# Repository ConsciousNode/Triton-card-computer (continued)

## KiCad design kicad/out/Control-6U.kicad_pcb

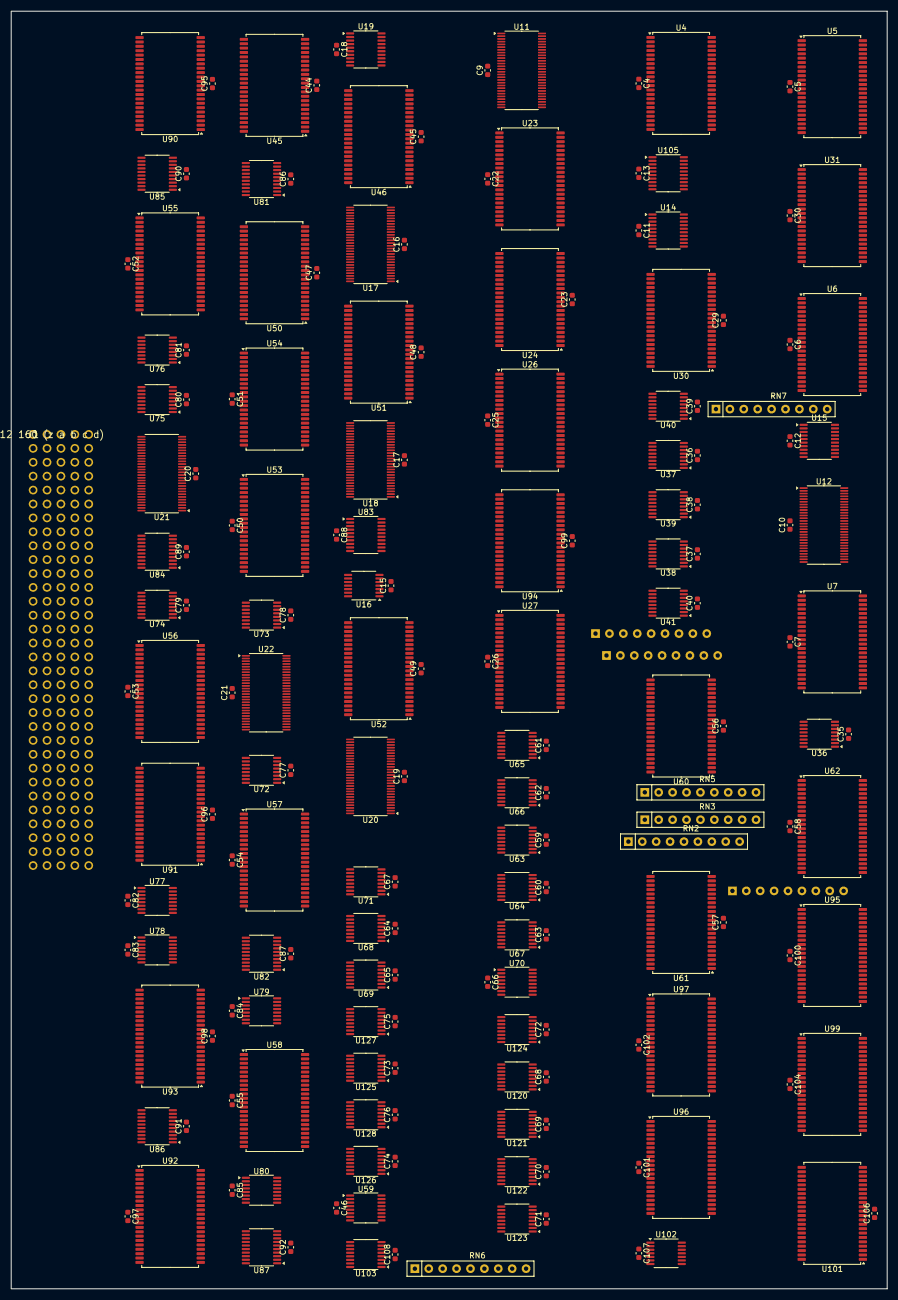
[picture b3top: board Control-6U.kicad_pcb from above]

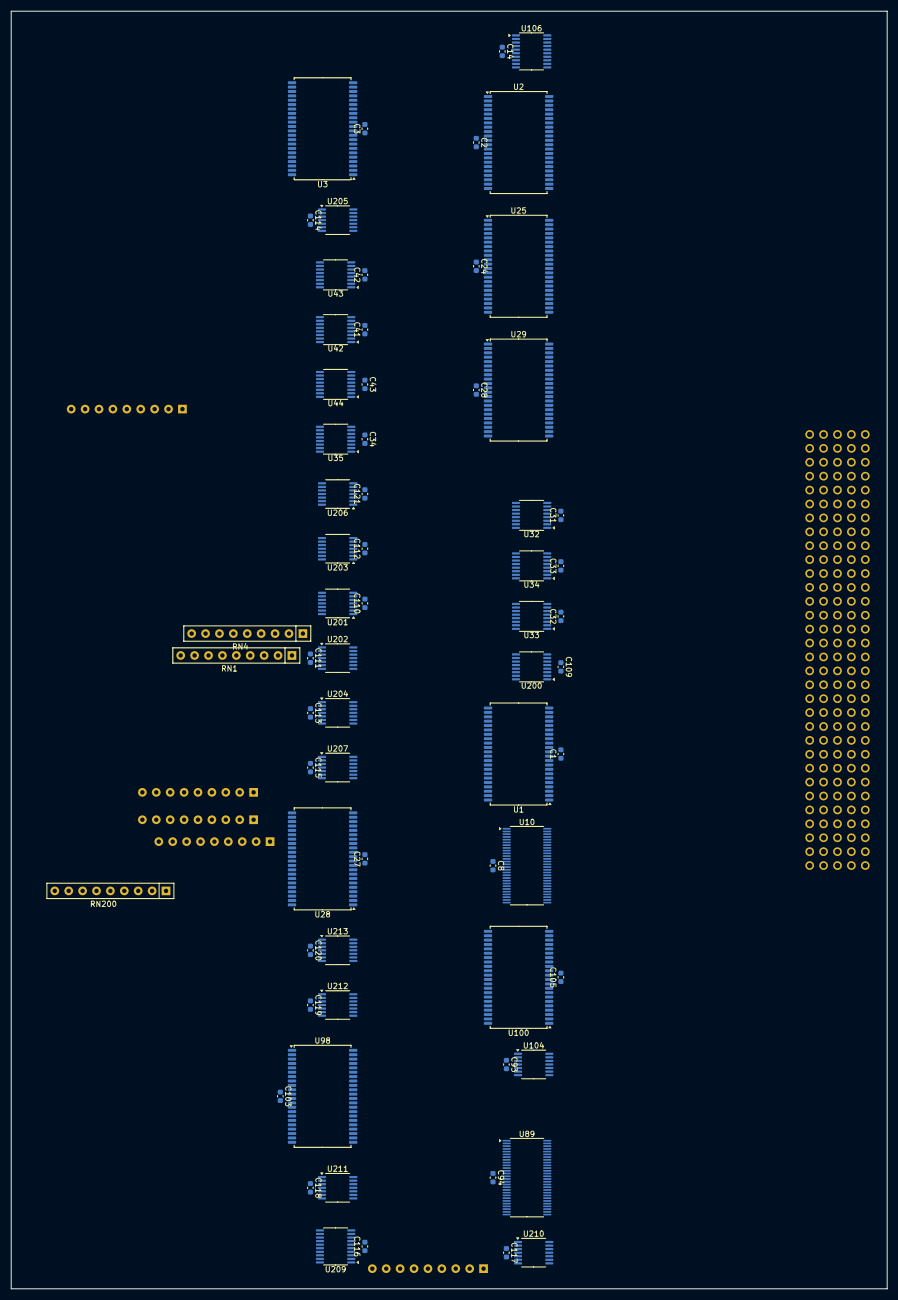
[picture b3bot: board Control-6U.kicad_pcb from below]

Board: 4 copper layers, 160.0 x 233.3 mm, 251 parts (67 on the bottom side), 680 nets, no tracks yet.

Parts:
C1, C2, C3, C4, C5, C6, C7, C8, C9, C10, C11, C12, C13, C14, C15, C16, C17, C18, C19, C20, C21, C22, C23, C24, C25, C26, C27, C28, C29, C30, C31, C32, C33, C34, C35, C36, C37, C38, C39, C40, C41, C42, C43, C44, C45, C46, C47, C48, C49, C50, C51, C52, C53, C54, C55, C56, C57, C58, C59, C60, C61, C62, C63, C64, C65, C66, C67, C68, C69, C70, C71, C72, C73, C74, C75, C76, C77, C78, C79, C80, C81, C82, C83, C84, C85, C86, C87, C88, C89, C90, C91, C92, C93, C94, C95, C96, C97, C98, C99, C100, C101, C102, C103, C104, C105, C106, C107, C108, C109, C110, C111, C112, C113, C114, C115, C116, C117, C118, C119, C120, C121: 100n; C_0603_1608Metric
J1: DIN41612 160 (z a b c d)
RN1, RN2, RN3, RN4, RN5, RN6, RN7: RPACK8; R_Array_SIP9
RN200: RPACK8G; R_Array_SIP9
U1, U2, U3, U4, U5, U6, U7, U23, U24, U25, U26, U27, U28, U29, U30, U31, U45, U46, U50, U51, U52, U53, U54, U55, U56, U57, U58, U60, U61, U62, U90, U91, U92, U93, U94, U95, U96, U97, U98, U99, U100, U101: IS61WV5128; TSOP-II-44_10.16x18.41mm_P0.8mm
U10, U11, U12, U17, U18, U20, U21, U22, U89: ALVCH16823; TSSOP-56_6.1x14mm_P0.5mm
U14, U15, U19, U209: LVC574; TSSOP-20_4.4x6.5mm_P0.65mm
U16, U203, U212: LVC32; TSSOP-14_4.4x5mm_P0.65mm
U32, U33, U34, U35, U36, U37, U38, U39, U40, U41, U42, U43, U44, U63, U64, U65, U66, U67, U68, U69, U70, U71, U120, U121, U122, U123, U124, U125, U126, U127, U128: LVC153; TSSOP-16_4.4x5mm_P0.65mm
U59, U72, U73, U74, U75, U76, U77, U78, U79, U80, U103: LVC157; TSSOP-16_4.4x5mm_P0.65mm
U81, U82, U83, U84, U85, U86, U87: LVC245; TSSOP-20_4.4x6.5mm_P0.65mm
U102, U202, U207, U211: LVC08; TSSOP-14_4.4x5mm_P0.65mm
U104, U201, U210: LVC04; TSSOP-14_4.4x5mm_P0.65mm
U105, U106: LVC244; TSSOP-20_4.4x6.5mm_P0.65mm
U200: LVC161; TSSOP-16_4.4x5mm_P0.65mm
U204, U205, U206, U213: LVC74; TSSOP-14_4.4x5mm_P0.65mm

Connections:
+3V3: C1.1, C2.1, C3.1, C4.1, C5.1, C6.1, C7.1, C8.1, C9.1, C10.1, C11.1, C12.1, C13.1, C14.1, C15.1, C16.1, C17.1, C18.1, C19.1, C20.1, C21.1, C22.1, C23.1, C24.1, C25.1, C26.1, C27.1, C28.1, C29.1, C30.1, C31.1, C32.1, C33.1, C34.1, C35.1, C36.1, C37.1, C38.1, C39.1, C40.1, C41.1, C42.1, C43.1, C44.1, C45.1, C46.1, C47.1, C48.1, C49.1, C50.1, C51.1, C52.1, C53.1, C54.1, C55.1, C56.1, C57.1, C58.1, C59.1, C60.1, C61.1, C62.1, C63.1, C64.1, C65.1, C66.1, C67.1, C68.1, C69.1, C70.1, C71.1, C72.1, C73.1, C74.1, C75.1, C76.1, C77.1, C78.1, C79.1, C80.1, C81.1, C82.1, C83.1, C84.1, C85.1, C86.1, C87.1, C88.1, C89.1, C90.1, C91.1, C92.1, C93.1, C94.1, C95.1, C96.1, C97.1, C98.1, C99.1, C100.1, C101.1, C102.1, C103.1, C104.1, C105.1, C106.1, C107.1, C108.1, C109.1, C110.1, C111.1, C112.1, C113.1, C114.1, C115.1, C116.1, C117.1, C118.1, C119.1, C120.1, C121.1, J1.z2, J1.z4, J1.z6, J1.z10, J1.z12, J1.z14, J1.z18, J1.z20, J1.z22, J1.z26, J1.z28, J1.z30, RN1.1, RN2.1, RN3.1, RN4.1, RN5.1, RN6.1, RN7.1, U1.11, U1.15, U1.33, U2.11, U2.15, U2.33, U3.11, U3.15, U3.33, U4.11, U4.15, U4.33, U5.11, U5.15, U5.33, U6.11, U6.15, U6.33, U7.11, U7.15, U7.33, U10.1, U10.7, U10.22, U10.28, U10.35, U10.50, U11.1, U11.7, U11.22, U11.28, U11.35, U11.50, U12.1, U12.7, U12.22, U12.28, U12.35, U12.50, U14.20, U15.20, U16.14, U17.1, U17.7, U17.22, U17.28, U17.35, U17.50, U18.1, U18.7, U18.22, U18.28, U18.35, U18.50, U19.20, U20.1, U20.7, U20.22, U20.28, U20.35, U20.50, U21.1, U21.7, U21.22, U21.28, U21.35, U21.50, U22.1, U22.7, U22.22, U22.28, U22.35, U22.50, U23.11, U23.15, U23.33, U24.11, U24.15, U24.33, U25.11, U25.15, U25.33, U26.11, U26.15, U26.33, U27.11, U27.15, U27.33, U28.11, U28.15, U28.33, U29.11, U29.15, U29.33, U30.11, U30.15, U30.33, U31.11, U31.15, U31.33, U32.3, U32.4, U32.11, U32.12, U32.13, U32.16, U33.3, U33.5, U33.11, U33.16, U34.3, U34.4, U34.11, U34.12, U34.16, U35.11, U35.12, U35.16, U36.4, U36.5, U36.13, U36.16, U37.16, U38.16, U39.16, U40.16, U41.16, U42.16, U43.16, U44.15, U44.16, U45.11, U45.15, U45.33, U46.11, U46.15, U46.33, U50.11, U50.15, U50.33, U51.11, U51.15, U51.33, U52.11, U52.15, U52.33, U53.11, U53.15, U53.33, U54.11, U54.15, U54.33, U55.11, U55.15, U55.33, U56.11, U56.15, U56.33, U57.11, U57.15, U57.33, U58.11, U58.15, U58.33, U59.2, U59.16, U60.11, U60.15, U60.33, U61.11, U61.15, U61.33, U62.11, U62.15, U62.33, U63.16, U64.16, U65.16, U66.16, U67.16, U68.16, U69.16, U70.16, U71.16, U72.16, U73.16, U74.16, U75.16, U76.16, U77.16, U78.16, U79.16, U80.16, U81.1, U81.20, U82.1, U82.20, U83.1, U83.20, U84.1, U84.20, U85.1, U85.20, U86.1, U86.20, U87.1, U87.20, U89.7, U89.22, U89.35, U89.50, U90.11, U90.15, U90.33, U91.11, U91.15, U91.33, U92.11, U92.15, U92.33, U93.11, U93.15, U93.33, U94.11, U94.15, U94.33, U95.11, U95.15, U95.33, U96.11, U96.15, U96.33, U97.11, U97.15, U97.33, U98.11, U98.15, U98.33, U99.11, U99.15, U99.33, U100.11, U100.15, U100.33, U101.11, U101.15, U101.33, U102.14, U103.16, U104.14, U105.20, U106.20, U120.16, U121.16, U122.16, U123.16, U124.16, U125.16, U126.16, U127.16, U128.16, U200.1, U200.7, U200.10, U200.16, U201.14, U202.14, U203.14, U204.1, U204.4, U204.10, U204.13, U204.14, U205.1, U205.13, U205.14, U206.1, U206.4, U206.10, U206.14, U207.14, U209.20, U210.14, U211.14, U212.14, U213.4, U213.10, U213.13, U213.14
+5V: J1.z8, J1.z16, J1.z24, J1.z32
/CBUSOE_F: U81.19, U82.19, U83.19, U84.19, U85.19, U86.19, U87.19, U103.4
/CEDGE: J1.c13, U200.9, U204.6
/HALTQ: U206.8, U207.5
/IR0LD: U16.3, U17.30, U17.55
/IR1LD: U16.6, U18.30, U18.55
/RESETC: U201.12, U206.13, U213.1
/RESET_C: U89.1, U89.28, U104.10
/RSTREQ: U201.8, U205.4, U205.10
/SCLK: U201.6, U204.11
/SPENT: U210.6, U211.13
/STEP2: U210.2, U211.2
/WSTB: J1.d1, U206.6
ABORT: J1.c15, U16.2, U16.5, U29.7, U46.30, U50.40, U51.40, U52.40, U53.40, U54.40, U55.40, U56.40, U57.40, U58.40, U95.17, U96.7, U97.7, U98.27
ALIAS: U23.32, U28.38
ALLOW: U207.13, U212.11
ALLOW0: U212.6, U212.12
BADADDR: J1.d2, U28.30
BTOPNZ: J1.c31, U28.19
CA0+: U63.7, U120.6
CA0-: U63.9, U120.10
CA1+: U64.7, U121.6
CA1-: U64.9, U121.10
CA2+: U65.7, U122.6
CA2-: U65.9, U122.10
CA3+: U66.7, U123.6
CA3-: U66.9, U123.10
CA4+: U67.7, U124.6
CA4-: U67.9, U124.10
CA5+: U68.7, U125.6
CA5-: U68.9, U125.10
CA6+: U69.7, U126.6
CA6-: U69.9, U126.10
CA7+: U70.7, U127.6
CA7-: U70.9, U127.10
CA8+: U71.7, U128.6
CA8-: U71.9, U128.10
CB0+: U81.2, U120.7
CB0-: U81.3, U120.9
CB1+: U81.4, U121.7
CB1-: U81.5, U121.9
CB2+: U81.6, U122.7
CB2-: U81.7, U122.9
CB3+: U81.8, U123.7
CB3-: U81.9, U123.9
CB4+: U82.2, U124.7
CB4-: U82.3, U124.9
CB5+: U82.4, U125.7
CB5-: U82.5, U125.9
CB6+: U82.6, U126.7
CB6-: U82.7, U126.9
CB7+: U82.8, U127.7
CB7-: U82.9, U127.9
CB8+: U83.2, U128.7
CB8-: U83.3, U128.9
CB9+: U72.4, U83.4
CB9-: U72.7, U83.5
CB10+: U72.9, U83.6
CB10-: U72.12, U83.7
CB11+: U73.4, U83.8
CB11-: U73.7, U83.9
CB12+: U73.9, U84.2
CB12-: U73.12, U84.3
CB13+: U74.4, U84.4
CB13-: U74.7, U84.5
CB14+: U74.9, U84.6
CB14-: U74.12, U84.7
CB15+: U75.4, U84.8
CB15-: U75.7, U84.9
CB16+: U75.9, U85.2
CB16-: U75.12, U85.3
CB17+: U76.4, U85.4
CB17-: U76.7, U85.5
CB18+: U76.9, U85.6
CB18-: U76.12, U85.7
CB19+: U77.4, U85.8
CB19-: U77.7, U85.9
CB20+: U77.9, U86.2
CB20-: U77.12, U86.3
CB21+: U78.4, U86.4
CB21-: U78.7, U86.5
CB22+: U78.9, U86.6
CB22-: U78.12, U86.7
CB23+: U79.4, U86.8
CB23-: U79.7, U86.9
CB24+: U79.9, U87.2
CB24-: U79.12, U87.3
CB25+: U80.4, U87.4
CB25-: U80.7, U87.5
CB26+: U80.9, U87.6
CB26-: U80.12, U87.7
CEDGE: U204.5, U207.4
CEDGE_NEXT: U202.6, U204.2
CEN: U202.10, U204.9, U211.9
CEN_D: U204.12, U207.8
CEN_D0: U207.6, U207.9
CLK: J1.c10, U10.29, U10.56, U11.29, U11.56, U12.29, U12.56, U14.11, U15.11, U17.29, U17.56, U18.29, U18.56, U19.11, U20.29, U20.56, U21.29, U21.56, U22.29, U22.56, U89.29, U89.56, U202.8, U205.3, U205.11, U206.11
COND: U28.9, U29.6
CSD0: U1.9, U10.54
CSD1: U1.10, U10.52
CSD2: U1.13, U10.51
CSD3: U1.14, U10.49
CSD4: U1.31, U10.48
CSD5: U1.32, U10.47
CSD6: U1.35, U10.45
CSD7: U1.36, U10.44
CSD8: U2.9, U10.43
CSD9: U2.10, U10.42
CSD10: U2.13, U10.41
CSD11: U2.14, U10.40
CSD12: U2.31, U10.38
CSD13: U2.32, U10.37
CSD14: U2.35, U10.36
CSD15: U2.36, U10.34
CSD16: U3.9, U10.33
CSD17: U3.10, U10.31
CSD18: U3.13, U11.54
CSD19: U3.14, U11.52
CSD20: U3.31, U11.51
CSD21: U3.32, U11.49
CSD22: U3.35, U11.48
CSD23: U3.36, U11.47
CSD24: U4.9, U11.45
CSD25: U4.10, U11.44
CSD26: U4.13, U11.43
CSD27: U4.14, U11.42
CSD28: U4.31, U11.41
CSD29: U4.32, U11.40
CSD30: U4.35, U11.38
CSD31: U4.36, U11.37
CSD32: U5.9, U11.36
CSD33: U5.10, U11.34
CSD34: U5.13, U11.33
CSD35: U5.14, U11.31
CSD36: U5.31, U12.54
CSD37: U5.32, U12.52
CSD38: U5.35, U12.51
CSD39: U5.36, U12.49
CSD40: U6.9, U12.48
CSD41: U6.10, U12.47
CSD42: U6.13, U12.45
CSD43: U6.14, U12.44
CSD44: U6.31, U12.43
CSD45: U6.32, U12.42
CSD46: U6.35, U12.41
CSD47: U6.36, U12.40
CSD48: U7.9, U12.38
CSD49: U7.10, U12.37
CSD50: U7.13, U12.36
CSD51: U7.14, U12.34
CSD52: U7.31, U12.33
CW_/ATF: RN7.6, U12.24, U211.5
CW_/CBUSOE: RN6.4, U12.12, U103.2
CW_/IR0CE: RN5.2, U11.21, U16.1
CW_/IR1CE: RN5.3, U11.23, U16.4
CW_/UPEN: RN6.5, U12.13, U72.15, U73.15, U74.15, U75.15, U76.15, U77.15, U78.15, U79.15, U80.15
CW_ACK: RN7.3, U12.20, U98.26
CW_BS0: RN6.2, U12.9, U63.14, U64.14, U65.14, U66.14, U67.14, U68.14, U69.14, U70.14, U71.14
CW_BS1: RN6.3, U12.10, U63.2, U64.2, U65.2, U66.2, U67.2, U68.2, U69.2, U70.2, U71.2
CW_BT0: RN7.4, U12.21, U120.14, U121.14, U122.14, U123.14, U124.14, U125.14, U126.14, U127.14, U128.14
CW_BT1: RN7.5, U12.23, U120.2, U121.2, U122.2, U123.2, U124.2, U125.2, U126.2, U127.2, U128.2
CW_C0: RN2.3, U10.15, U37.5, U60.3, U61.3, U62.3
CW_C1: RN2.4, U10.16, U37.11, U60.4, U61.4, U62.4
CW_C2: RN2.5, U10.17, U38.5, U60.5, U61.5, U62.5
CW_C3: RN2.6, U10.19, U38.11, U60.6, U61.6, U62.6
CW_C4: RN2.7, U10.20, U39.5, U60.7, U61.7, U62.7
CW_C5: RN2.8, U10.21, U39.11, U60.16, U61.16, U62.16
CW_C6: RN2.9, U10.23, U40.5, U60.17, U61.17, U62.17
CW_C7: RN3.2, U10.24, U40.11, U60.18, U61.18, U62.18
CW_C8: RN3.3, U10.26, U41.5, U60.19, U61.19, U62.19
CW_C9: RN3.4, U11.3, U41.11, U60.20, U61.20, U62.20
CW_C10: RN3.5, U11.5, U60.26, U61.26, U62.26
CW_C11: RN3.6, U11.6, U60.27, U61.27, U62.27
CW_C12: RN3.7, U11.8, U60.28, U61.28, U62.28
CW_C13: RN3.8, U11.9, U60.29, U61.29, U62.29
CW_CD0: RN1.7, U10.10, U28.3
CW_CD1: RN1.8, U10.12, U28.4
CW_CD2: RN1.9, U10.13, U28.5
CW_CD3: RN2.2, U10.14, U28.6
CW_CFETCH: RN1.5, U10.8, U29.18
CW_FS0: RN4.3, U11.13, U42.6
CW_FS1: RN4.4, U11.14, U42.10
CW_FS2: RN4.5, U11.15, U43.6
CW_FS3: RN4.6, U11.16, U43.10
CW_FS4: RN4.7, U11.17, U44.6
CW_PCC+: RN5.6, U12.3, U50.28
CW_PCC-: RN5.7, U12.5, U50.29
CW_PCOP0: RN5.4, U11.24, U50.30, U51.30, U52.30, U53.30, U54.30, U55.30, U56.30, U57.30, U58.30
CW_PCOP1: RN5.5, U11.26, U50.38, U51.38, U52.38, U53.38, U54.38, U55.38, U56.38, U57.38, U58.38
CW_PSW0: RN6.9, U12.17, U95.7
CW_PSW1: RN7.2, U12.19, U95.16
CW_RET: RN1.6, U10.9, U29.17
CW_RFBUS: RN6.8, U12.16, U102.2
CW_RSK0: RN4.8, U11.19, U23.3
CW_RSK1: RN4.9, U11.20, U23.4
CW_SLS0: RN3.9, U11.10, U42.14, U43.14, U44.14
CW_SLS1: RN4.2, U11.12, U42.2, U43.2, U44.2
CW_SPR: RN6.7, U12.15, U94.41
CW_SPRWR: RN6.6, U12.14, U95.3, U96.3, U97.3
CW_SQ0: RN1.2, U10.3, U29.3
CW_SQ1: RN1.3, U10.5, U29.4
CW_SQ2: RN1.4, U10.6, U29.5
CW_UOP0: RN5.8, U12.6, U46.17
CW_UOP1: RN5.9, U12.8, U46.18
D0+: J1.a1, U17.54, U18.54, U45.3, U50.17, U81.18, U90.3
D0-: J1.a2, U17.52, U18.52, U45.4, U50.18, U81.17, U90.4
D1+: J1.a3, U17.51, U18.51, U45.5, U50.19, U81.16, U90.5
D1-: J1.a4, U17.49, U18.49, U45.6, U50.20, U81.15, U90.6
D2+: J1.a5, U17.48, U18.48, U45.7, U50.26, U81.14, U90.7
D2-: J1.a6, U17.47, U18.47, U45.16, U50.27, U81.13, U90.16
D3+: J1.a7, U17.45, U18.45, U45.17, U51.17, U81.12, U90.17, U95.19
D3-: J1.a9, U17.44, U18.44, U45.18, U51.18, U81.11, U90.18, U95.20
D4+: J1.a10, U17.43, U18.43, U51.19, U82.18, U90.19, U95.26
D4-: J1.a11, U17.42, U18.42, U51.20, U82.17, U90.20, U95.27
D5+: J1.a12, U17.41, U18.41, U51.26, U82.16, U90.26
D5-: J1.a13, U17.40, U18.40, U51.27, U82.15, U90.27
D6+: J1.a14, U17.38, U18.38, U52.17, U82.14, U90.28
D6-: J1.a15, U17.37, U18.37, U52.18, U82.13, U90.29
D7+: J1.a17, U17.36, U18.36, U52.19, U82.12, U90.30
D7-: J1.a18, U17.34, U18.34, U52.20, U82.11, U90.38
D8+: J1.a19, U17.33, U18.33, U52.26, U83.18, U90.39
D8-: J1.a20, U17.31, U18.31, U52.27, U83.17, U90.40
D9+: J1.a21, U53.17, U83.16, U91.3
D9-: J1.a22, U53.18, U83.15, U91.4
D10+: J1.a23, U53.19, U83.14, U91.5
D10-: J1.a25, U53.20, U83.13, U91.6
D11+: J1.a26, U53.26, U83.12, U91.7
D11-: J1.a27, U53.27, U83.11, U91.16
D12+: J1.a28, U54.17, U84.18, U91.17
D12-: J1.a29, U54.18, U84.17, U91.18
D13+: J1.a30, U54.19, U84.16, U91.19
D13-: J1.a31, U54.20, U84.15, U91.20
D14+: J1.b1, U54.26, U84.14, U91.26
D14-: J1.b2, U54.27, U84.13, U91.27
D15+: J1.b3, U55.17, U84.12, U91.28
D15-: J1.b4, U55.18, U84.11, U91.29
D16+: J1.b5, U55.19, U85.18, U91.30
D16-: J1.b6, U55.20, U85.17, U91.38
D17+: J1.b7, U55.26, U85.16, U91.39
D17-: J1.b9, U55.27, U85.15, U91.40
D18+: J1.b10, U56.17, U85.14, U92.3
D18-: J1.b11, U56.18, U85.13, U92.4
D19+: J1.b12, U56.19, U85.12, U92.5
D19-: J1.b13, U56.20, U85.11, U92.6
D20+: J1.b14, U56.26, U86.18, U92.7
D20-: J1.b15, U56.27, U86.17, U92.16
D21+: J1.b17, U57.17, U86.16, U92.17
D21-: J1.b18, U57.18, U86.15, U92.18
D22+: J1.b19, U57.19, U86.14, U92.19
D22-: J1.b20, U57.20, U86.13, U92.20
D23+: J1.b21, U57.26, U86.12, U92.26
D23-: J1.b22, U57.27, U86.11, U92.27
D24+: J1.b23, U58.17, U87.18, U92.28
D24-: J1.b25, U58.18, U87.17, U92.29
D25+: J1.b26, U58.19, U87.16, U92.30
D25-: J1.b27, U58.20, U87.15, U92.38
D26+: J1.b28, U58.26, U87.14, U92.39
D26-: J1.b29, U58.27, U87.13, U92.40
DP0: U26.9, U37.4
DP1: U26.10, U37.12
DP2: U26.13, U38.4
DP3: U26.14, U38.12
DP4: U26.31, U39.4
DP5: U26.32, U39.12
DP6: U26.35, U40.4
DP7: U26.36, U40.12
DP8: U27.9, U41.4
DP9: U27.10, U41.12
DS0: U23.9, U42.5
DS1: U23.10, U42.11
DS2: U23.13, U43.5
DS3: U23.14, U43.11
DS4: U23.31, U44.5
FIX0: U32.7, U37.3
FIX1: U32.9, U37.13
FIX2: U33.7, U38.3
FIX3: U33.9, U38.13
FIX4: U34.7, U39.3
FIX5: U34.9, U39.13
FIX6: U35.7, U40.3
FIX7: U35.9, U40.13
FIX8: U36.7, U41.3
FIX9: U36.9, U41.13
FK: J1.c17, U29.16
FP_RUN: J1.d28, U209.2
FP_STEP: J1.d29, U209.4
FP_STEPMODE: J1.d30, U209.7
FX0: U29.13, U32.14, U33.14, U34.14, U35.14, U36.14
FX1: U29.14, U32.2, U33.2, U34.2, U35.2, U36.2
GND: C1.2, C2.2, C3.2, C4.2, C5.2, C6.2, C7.2, C8.2, C9.2, C10.2, C11.2, C12.2, C13.2, C14.2, C15.2, C16.2, C17.2, C18.2, C19.2, C20.2, C21.2, C22.2, C23.2, C24.2, C25.2, C26.2, C27.2, C28.2, C29.2, C30.2, C31.2, C32.2, C33.2, C34.2, C35.2, C36.2, C37.2, C38.2, C39.2, C40.2, C41.2, C42.2, C43.2, C44.2, C45.2, C46.2, C47.2, C48.2, C49.2, C50.2, C51.2, C52.2, C53.2, C54.2, C55.2, C56.2, C57.2, C58.2, C59.2, C60.2, C61.2, C62.2, C63.2, C64.2, C65.2, C66.2, C67.2, C68.2, C69.2, C70.2, C71.2, C72.2, C73.2, C74.2, C75.2, C76.2, C77.2, C78.2, C79.2, C80.2, C81.2, C82.2, C83.2, C84.2, C85.2, C86.2, C87.2, C88.2, C89.2, C90.2, C91.2, C92.2, C93.2, C94.2, C95.2, C96.2, C97.2, C98.2, C99.2, C100.2, C101.2, C102.2, C103.2, C104.2, C105.2, C106.2, C107.2, C108.2, C109.2, C110.2, C111.2, C112.2, C113.2, C114.2, C115.2, C116.2, C117.2, C118.2, C119.2, C120.2, C121.2, J1.a8, J1.a16, J1.a24, J1.a32, J1.b8, J1.b16, J1.b24, J1.b32, J1.c8, J1.c16, J1.c24, J1.c32, J1.d8, J1.d16, J1.d24, J1.d32, J1.z1, J1.z3, J1.z5, J1.z7, J1.z9, J1.z11, J1.z13, J1.z15, J1.z17, J1.z19, J1.z21, J1.z23, J1.z25, J1.z27, J1.z29, J1.z31, RN200.1, U1.8, U1.12, U1.26, U1.27, U1.28, U1.29, U1.30, U1.34, U1.37, U1.38, U1.39, U1.40, U1.41, U2.8, U2.12, U2.26, U2.27, U2.28, U2.29, U2.30, U2.34, U2.37, U2.38, U2.39, U2.40, U2.41, U3.8, U3.12, U3.26, U3.27, U3.28, U3.29, U3.30, U3.34, U3.37, U3.38, U3.39, U3.40, U3.41, U4.8, U4.12, U4.26, U4.27, U4.28, U4.29, U4.30, U4.34, U4.37, U4.38, U4.39, U4.40, U4.41, U5.8, U5.12, U5.26, U5.27, U5.28, U5.29, U5.30, U5.34, U5.37, U5.38, U5.39, U5.40, U5.41, U6.8, U6.12, U6.26, U6.27, U6.28, U6.29, U6.30, U6.34, U6.37, U6.38, U6.39, U6.40, U6.41, U7.8, U7.12, U7.26, U7.27, U7.28, U7.29, U7.30, U7.34, U7.37, U7.38, U7.39, U7.40, U7.41, U10.4, U10.11, U10.18, U10.25, U10.30, U10.32, U10.39, U10.46, U10.53, U10.55, U11.4, U11.11, U11.18, U11.25, U11.30, U11.32, U11.39, U11.46, U11.53, U11.55, U12.4, U12.11, U12.18, U12.25, U12.30, U12.31, U12.32, U12.39, U12.46, U12.53, U12.55, U14.1, U14.10, U15.1, U15.4, U15.5, U15.6, U15.7, U15.8, U15.9, U15.10, U16.7, U16.9, U16.10, U16.12, U16.13, U17.2, U17.4, U17.11, U17.18, U17.25, U17.27, U17.32, U17.39, U17.46, U17.53, U18.2, U18.4, U18.11, U18.18, U18.25, U18.27, U18.32, U18.39, U18.46, U18.53, U19.1, U19.9, U19.10, U20.2, U20.4, U20.11, U20.18, U20.25, U20.27, U20.30, U20.32, U20.39, U20.46, U20.53, U20.55, U21.2, U21.4, U21.11, U21.18, U21.25, U21.27, U21.30, U21.32, U21.39, U21.46, U21.53, U21.55, U22.2, U22.4, U22.11, U22.18, U22.25, U22.27, U22.30, U22.32, U22.39, U22.46, U22.53, U22.55, U23.8, U23.12, U23.30, U23.34, U23.37, U23.38, U23.39, U23.40, U23.41, U24.8, U24.12, U24.34, U24.37, U24.41, U25.8, U25.12, U25.34, U25.37, U25.41, U26.8, U26.12, U26.27, U26.28, U26.29, U26.30, U26.34, U26.37, U26.38, U26.39, U26.40, U26.41, U27.8, U27.12, U27.27, U27.28, U27.29, U27.30, U27.34, U27.37, U27.38, U27.39, U27.40, U27.41, U28.8, U28.12, U28.34, U28.37, U28.39, U28.40, U28.41, U29.8, U29.12, U29.26, U29.27, U29.28, U29.29, U29.30, U29.34, U29.37, U29.38, U29.39, U29.40, U29.41, U30.8, U30.12, U30.27, U30.28, U30.29, U30.30, U30.34, U30.37, U30.38, U30.39, U30.40, U30.41, U31.8, U31.12, U31.27, U31.28, U31.29, U31.30, U31.34, U31.37, U31.38, U31.39, U31.40, U31.41, U32.1, U32.5, U32.6, U32.8, U32.10, U32.15, U33.1, U33.4, U33.6, U33.8, U33.10, U33.12, U33.13, U33.15, U34.1, U34.5, U34.6, U34.8, U34.10, U34.13, U34.15, U35.1, U35.3, U35.4, U35.5, U35.6, U35.8, U35.10, U35.13, U35.15, U36.1, U36.3, U36.6, U36.8, U36.10, U36.11, U36.12, U36.15, U37.1, U37.8, U37.15, U38.1, U38.8, U38.15, U39.1, U39.8, U39.15, U40.1, U40.8, U40.15, U41.1, U41.8, U41.15, U42.1, U42.3, U42.8, U42.13, U42.15, U43.1, U43.3, U43.8, U43.13, U43.15, U44.1, U44.3, U44.8, U44.10, U44.11, U44.12, U44.13, U45.8, U45.12, U45.19, U45.20, U45.26, U45.27, U45.28, U45.29, U45.30, U45.34, U45.37, U45.38, U45.39, U45.40, U45.41, U46.8, U46.12, U46.34, U46.37, U46.38, U46.39, U46.40, U46.41, U50.8, U50.12, U50.34, U50.37, U50.39, U50.41, U51.8, U51.12, U51.34, U51.37, U51.39, U51.41, U52.8, U52.12, U52.34, U52.37, U52.39, U52.41, U53.8, U53.12, U53.34, U53.37, U53.41, U54.8, U54.12, U54.34, U54.37, U54.41, U55.8, U55.12, U55.34, U55.37, U55.41, U56.8, U56.12, U56.34, U56.37, U56.41, U57.8, U57.12, U57.34, U57.37, U57.41, U58.8, U58.12, U58.34, U58.37, U58.41, U59.3, U59.5, U59.6, U59.8, U59.10, U59.11, U59.13, U59.14, U59.15, U60.8, U60.12, U60.30, U60.34, U60.37, U60.38, U60.39, U60.40, U60.41, U61.8, U61.12, U61.30, U61.34, U61.37, U61.38, U61.39, U61.40, U61.41, U62.8, U62.12, U62.30, U62.34, U62.37, U62.38, U62.39, U62.40, U62.41, U63.1, U63.8, U63.15, U64.1, U64.8, U64.15, U65.1, U65.8, U65.15, U66.1, U66.8, U66.15, U67.1, U67.8, U67.15, U68.1, U68.3, U68.8, U68.13, U68.15, U69.1, U69.3, U69.8, U69.13, U69.15, U70.1, U70.3, U70.8, U70.13, U70.15, U71.1, U71.3, U71.8, U71.13, U71.15, U72.1, U72.3, U72.6, U72.8, U72.10, U72.13, U73.1, U73.3, U73.6, U73.8, U73.10, U73.13, U74.1, U74.3, U74.6, U74.8, U74.10, U74.13, U75.1, U75.3, U75.6, U75.8, U75.10, U75.13, U76.1, U76.3, U76.6, U76.8, U76.10, U76.13, U77.1, U77.3, U77.6, U77.8, U77.10, U77.13, U78.1, U78.3, U78.6, U78.8, U78.10, U78.13, U79.1, U79.3, U79.6, U79.8, U79.10, U79.13, U80.1, U80.3, U80.6, U80.8, U80.10, U80.13, U81.10, U82.10, U83.10, U84.10, U85.10, U86.10, U87.8, U87.9, U87.10, U89.2, U89.4, U89.11, U89.18, U89.25, U89.27, U89.30, U89.31, U89.32, U89.33, U89.34, U89.39, U89.46, U89.53, U89.55, U90.8, U90.12, U90.34, U90.37, U90.41, U91.8, U91.12, U91.34, U91.37, U91.41, U92.8, U92.12, U92.34, U92.37, U92.41, U93.8, U93.12, U93.34, U93.37, U93.41, U94.8, U94.12, U94.34, U94.37, U95.8, U95.12, U95.34, U95.37, U95.40, U95.41, U96.8, U96.12, U96.34, U96.37, U96.38, U96.39, U96.40, U96.41, U97.8, U97.12, U97.34, U97.37, U97.38, U97.39, U97.40, U97.41, U98.8, U98.12, U98.34, U98.37, U98.40, U98.41, U99.8, U99.12, U99.28, U99.29, U99.30, U99.34, U99.37, U99.38, U99.39, U99.40, U99.41, U100.8, U100.12, U100.28, U100.29, U100.30, U100.34, U100.37, U100.38, U100.39, U100.40, U100.41, U101.8, U101.12, U101.34, U101.37, U101.41, U102.4, U102.5, U102.7, U102.9, U102.10, U102.12, U102.13, U103.3, U103.5, U103.6, U103.8, U103.10, U103.11, U103.13, U103.14, U103.15, U104.7, U104.13, U105.1, U105.10, U105.19, U106.1, U106.6, U106.8, U106.10, U106.11, U106.13, U106.15, U106.17, U106.19, U120.1, U120.3, U120.8, U120.13, U120.15, U121.1, U121.3, U121.8, U121.13, U121.15, U122.1, U122.3, U122.8, U122.13, U122.15, U123.1, U123.3, U123.5, U123.8, U123.11, U123.13, U123.15, U124.1, U124.3, U124.4, U124.5, U124.8, U124.11, U124.12, U124.13, U124.15, U125.1, U125.3, U125.4, U125.5, U125.8, U125.11, U125.12, U125.13, U125.15, U126.1, U126.3, U126.4, U126.5, U126.8, U126.11, U126.12, U126.13, U126.15, U127.1, U127.3, U127.4, U127.5, U127.8, U127.11, U127.12, U127.13, U127.15, U128.1, U128.3, U128.4, U128.5, U128.8, U128.11, U128.12, U128.13, U128.15, U200.3, U200.4, U200.5, U200.6, U200.8, U201.7, U202.7, U203.7, U203.12, U203.13, U204.7, U205.2, U205.7, U206.7, U207.7, U209.1, U209.9, U209.10, U210.7, U210.9, U210.11, U210.13, U211.7, U212.7, U213.7
GOQ: U207.10, U213.9
HALTED: U29.32, U203.9
HALTQ: U203.10, U206.9
HALT_D: U203.8, U206.12
HOLD: U29.31, U30.26, U31.26
IDLEOK: U210.3, U211.6, U212.5
IE: J1.d26, U89.6, U95.30, U99.27, U101.16
IE_N: U89.51, U95.13, U100.27
IM0: U89.10, U96.26, U99.16, U101.19
IM0_N: U89.47, U96.9, U98.16, U100.16
IM1: U89.12, U96.27, U99.17, U101.20
IM1_N: U89.45, U96.10, U98.17, U100.17
IM2: U89.13, U96.28, U99.18, U101.26
IM2_N: U89.44, U96.13, U98.18, U100.18
IM3: U89.14, U96.29, U99.19, U101.27
IM3_N: U89.43, U96.14, U98.19, U100.19
IM4: U89.15, U96.30, U99.20, U101.28
IM4_N: U89.42, U96.31, U98.20, U100.20
INC0: U30.9, U37.6
INC1: U30.10, U37.10
INC2: U30.13, U38.6
INC3: U30.14, U38.10
INC4: U30.31, U39.6
INC5: U30.32, U39.10
INC6: U30.35, U40.6
INC7: U30.36, U40.10
INC8: U31.9, U41.6
INC9: U31.10, U41.10
IORDY: J1.d4, U29.20
IP0: U89.16, U97.26, U99.3, U101.29
IP0_A: U97.9, U98.3
IP0_N: U89.41, U98.9, U100.3
IP1: U89.17, U97.27, U99.4, U101.30
IP1_A: U97.10, U98.4
IP1_N: U89.40, U98.10, U100.4
IP2: U89.19, U97.28, U99.5, U101.38
IP2_A: U97.13, U98.5
IP2_N: U89.38, U98.13, U100.5
IP3: U89.20, U97.29, U99.6, U101.39
IP3_A: U97.14, U98.6
IP3_N: U89.37, U98.14, U100.6
IP4: U89.21, U97.30, U99.7, U101.40
IP4_A: U97.31, U98.7
IP4_N: U89.36, U98.31, U100.7
IR0_0+: U17.3, U23.5
IR0_0-: U17.5, U23.6
IR0_1+: U17.6, U23.7
IR0_1-: U17.8, U23.16
IR0_2+: U17.9, U23.17
IR0_2-: U17.10, U23.18
IR0_3+: U17.12, U23.19
IR0_3-: U17.13, U23.20
IR0_4+: U17.14, U26.3, U27.3, U63.3
IR0_4-: U17.15, U26.4, U27.4, U63.13
IR0_5+: U17.16, U26.5, U27.5, U64.3
IR0_5-: U17.17, U26.6, U27.6, U64.13
IR0_6+: U17.19, U26.7, U27.7, U65.3
IR0_6-: U17.20, U26.16, U27.16, U65.13
IR0_7+: U17.21, U26.17, U27.17, U66.3
IR0_7-: U17.23, U26.18, U27.18, U66.13
IR0_8+: U17.24, U26.19, U27.19, U67.3
IR0_8-: U17.26, U26.20, U27.20, U67.13
IR1_0+: U18.3, U23.26, U24.3, U25.3, U63.5, U94.3
IR1_0-: U18.5, U23.27, U24.4, U25.4, U63.11, U94.4
IR1_1+: U18.6, U23.28, U24.5, U25.5, U64.5, U94.5
IR1_1-: U18.8, U23.29, U24.6, U25.6, U64.11, U94.6
IR1_2+: U18.9, U24.7, U25.7, U65.5, U94.7
IR1_2-: U18.10, U24.16, U25.16, U65.11, U94.16
IR1_3+: U18.12, U24.17, U25.17, U66.5, U94.17
IR1_3-: U18.13, U24.18, U25.18, U66.11, U94.18
IR1_4+: U18.14, U24.19, U25.19, U67.5, U94.19
IR1_4-: U18.15, U24.20, U25.20, U67.11, U94.20
IR1_5+: U18.16, U24.26, U25.26, U68.5, U94.26
IR1_5-: U18.17, U24.27, U25.27, U68.11, U94.27
IR1_6+: U18.19, U24.28, U25.28, U69.5, U94.28
IR1_6-: U18.20, U24.29, U25.29, U69.11, U94.29
IR1_7+: U18.21, U24.30, U25.30, U70.5, U94.30
IR1_7-: U18.23, U24.38, U25.38, U70.11, U94.38
IR1_8+: U18.24, U24.39, U25.39, U71.5, U94.39
IR1_8-: U18.26, U24.40, U25.40, U71.11, U94.40
IRQN: U29.19, U100.35
IRQP: U28.26, U99.35
IRQSET0: J1.d5, U98.28
IRQSET1: J1.d6, U98.29
IRQSET2: J1.d7, U98.30
IRQSET3: J1.d9, RN200.3, U98.38
IRQSET4: J1.d10, RN200.4, U98.39
IV0+: U99.9, U120.5
IV0-: U99.10, U120.11
IV1+: U99.13, U121.5
IV1-: U99.14, U121.11
IV2+: U99.31, U122.5
IV2-: U99.32, U122.11
KV0: U60.9, U63.4
KV1: U60.10, U63.12
KV2: U60.13, U64.4
KV3: U60.14, U64.12
KV4: U60.31, U65.4
KV5: U60.32, U65.12
KV6: U60.35, U66.4
KV7: U60.36, U66.12
KV8: U61.9, U67.4
KV9: U61.10, U67.12
KV10: U61.13, U68.4
KV11: U61.14, U68.12
KV12: U61.31, U69.4
KV13: U61.32, U69.12
KV14: U61.35, U70.4
KV15: U61.36, U70.12
KV16: U62.9, U71.4
KV17: U62.10, U71.12
LID0: U94.9, U95.4, U96.4, U97.4, U101.3
LID1: U94.10, U95.5, U96.5, U97.5, U101.4
LID2: U94.13, U95.6, U96.6, U97.6, U101.5
LOAD: J1.c19, U203.5
LONGOK: U202.5, U203.3, U207.2
LV0: U45.9, U46.19
LV1: U45.10, U46.20
LV2: U45.13, U46.26
LV3: U45.14, U46.27
LV4: U45.31, U46.28
LV5: U45.32, U46.29
MOD0: U93.9, U96.16, U97.16
MOD1: U93.10, U96.17, U97.17
MOD2: U93.13, U96.18, U97.18
MOD3: U93.14, U96.19, U97.19
MOD4: U93.31, U96.20, U97.20
MODE: J1.d23, U26.26, U27.26, U28.28, U59.1, U95.28, U99.26, U101.6, U104.4
MODE1: U209.8, U209.14
MODE2: U209.13, U211.4
MODE_I: U89.3, U104.3
MODE_N: U95.9, U100.26, U104.1
MODE_NI: U89.54, U104.2
MS0: U29.9, U37.14, U38.14, U39.14, U40.14, U41.14
MS1: U29.10, U37.2, U38.2, U39.2, U40.2, U41.2
NA0: U14.2, U37.7, U105.2
NA1: U14.3, U37.9, U105.4
NA2: U14.4, U38.7, U105.6
NA3: U14.5, U38.9, U105.8
NA4: U14.6, U39.7, U105.11
NA5: U14.7, U39.9, U105.13
NA6: U14.8, U40.7, U105.15
NA7: U14.9, U40.9, U105.17
NA8: U15.2, U41.7, U106.2
NA9: U15.3, U41.9, U106.4
NZ: U93.32, U95.18
PC0+: U20.3, U50.3, U63.6
PC0-: U20.5, U50.4, U63.10
PC1+: U20.6, U50.5, U64.6
PC1-: U20.8, U50.6, U64.10
PC2+: U20.9, U50.7, U65.6
PC2-: U20.10, U50.16, U65.10
PC3+: U20.12, U51.3, U66.6
PC3-: U20.13, U51.4, U66.10
PC4+: U20.14, U51.5, U67.6
PC4-: U20.15, U51.6, U67.10
PC5+: U20.16, U51.7, U68.6
PC5-: U20.17, U51.16, U68.10
PC6+: U20.19, U52.3, U69.6
PC6-: U20.20, U52.4, U69.10
PC7+: U20.21, U52.5, U70.6
PC7-: U20.23, U52.6, U70.10
PC8+: U20.24, U52.7, U71.6
PC8-: U20.26, U52.16, U71.10
PC9+: U21.3, U53.3, U72.2
PC9-: U21.5, U53.4, U72.5
PC10+: U21.6, U53.5, U72.11
PC10-: U21.8, U53.6, U72.14
PC11+: U21.9, U53.7, U73.2
PC11-: U21.10, U53.16, U73.5
PC12+: U21.12, U54.3, U73.11
PC12-: U21.13, U54.4, U73.14
PC13+: U21.14, U54.5, U74.2
PC13-: U21.15, U54.6, U74.5
PC14+: U21.16, U54.7, U74.11
PC14-: U21.17, U54.16, U74.14
PC15+: U21.19, U55.3, U75.2
PC15-: U21.20, U55.4, U75.5
PC16+: U21.21, U55.5, U75.11
PC16-: U21.23, U55.6, U75.14
PC17+: U21.24, U55.7, U76.2
PC17-: U21.26, U55.16, U76.5
PC18+: U22.3, U56.3, U76.11
PC18-: U22.5, U56.4, U76.14
PC19+: U22.6, U56.5, U77.2
PC19-: U22.8, U56.6, U77.5
PC20+: U22.9, U56.7, U77.11
PC20-: U22.10, U56.16, U77.14
PC21+: U22.12, U57.3, U78.2
PC21-: U22.13, U57.4, U78.5
PC22+: U22.14, U57.5, U78.11
PC22-: U22.15, U57.6, U78.14
PC23+: U22.16, U57.7, U79.2
PC23-: U22.17, U57.16, U79.5
PC24+: U22.19, U58.3, U79.11
PC24-: U22.20, U58.4, U79.14
PC25+: U22.21, U58.5, U80.2
PC25-: U22.23, U58.6, U80.5
PC26+: U22.24, U58.7, U80.11
PC26-: U22.26, U58.16, U80.14
PCY1+: U50.35, U51.28
PCY1-: U50.36, U51.29
PCY2+: U51.35, U52.28
PCY2-: U51.36, U52.29
PCY3+: U52.35, U53.28
PCY3-: U52.36, U53.29
PCY4+: U53.35, U54.28
PCY4-: U53.36, U54.29
PCY5+: U54.35, U55.28
PCY5-: U54.36, U55.29
PCY6+: U55.35, U56.28
PCY6-: U55.36, U56.29
PCY7+: U56.35, U57.28
PCY7-: U56.36, U57.29
PCY8+: U57.35, U58.28
PCY8-: U57.36, U58.29
PEND: U211.12, U212.2, U213.5
PEND_D: U212.8, U213.2
PKEEP: U211.11, U212.10
PN0+: U20.54, U50.9
PN0-: U20.52, U50.10
PN1+: U20.51, U50.13
PN1-: U20.49, U50.14
PN2+: U20.48, U50.31
PN2-: U20.47, U50.32
PN3+: U20.45, U51.9
PN3-: U20.44, U51.10
PN4+: U20.43, U51.13
PN4-: U20.42, U51.14
PN5+: U20.41, U51.31
PN5-: U20.40, U51.32
PN6+: U20.38, U52.9
PN6-: U20.37, U52.10
PN7+: U20.36, U52.13
PN7-: U20.34, U52.14
PN8+: U20.33, U52.31
PN8-: U20.31, U52.32
PN9+: U21.54, U53.9
PN9-: U21.52, U53.10
PN10+: U21.51, U53.13
PN10-: U21.49, U53.14
PN11+: U21.48, U53.31
PN11-: U21.47, U53.32
PN12+: U21.45, U54.9
PN12-: U21.44, U54.10
PN13+: U21.43, U54.13
PN13-: U21.42, U54.14
PN14+: U21.41, U54.31
PN14-: U21.40, U54.32
PN15+: U21.38, U55.9
PN15-: U21.37, U55.10
PN16+: U21.36, U55.13
PN16-: U21.34, U55.14
PN17+: U21.33, U55.31
PN17-: U21.31, U55.32
PN18+: U22.54, U56.9
PN18-: U22.52, U56.10
PN19+: U22.51, U56.13
PN19-: U22.49, U56.14
PN20+: U22.48, U56.31
PN20-: U22.47, U56.32
PN21+: U22.45, U57.9
PN21-: U22.44, U57.10
PN22+: U22.43, U57.13
PN22-: U22.42, U57.14
PN23+: U22.41, U57.31
PN23-: U22.40, U57.32
PN24+: U22.38, U58.9
PN24-: U22.37, U58.10
PN25+: U22.36, U58.13
PN25-: U22.34, U58.14
PN26+: U22.33, U58.31
PN26-: U22.31, U58.32
PORT0: J1.d17, U25.9
PORT1: J1.d18, U25.10
PORT2: J1.d19, U25.13
PORT3: J1.d20, U25.14
PORT4: J1.d21, U25.31
PORT5: J1.d22, U25.32
PRIV: J1.d25, U28.27, U89.5, U95.29, U101.7
PRIV_N: U89.52, U95.10
PROTEN: J1.d27, U95.38, U101.17, U104.8
PROTEN_I: U89.8, U104.9
PROTEN_N: U95.14, U104.5
PROTEN_NI: U89.49, U104.6
QT+: J1.c29, U28.17
QT-: J1.c30, U28.18
RESET: J1.c12, U10.2, U10.27, U11.2, U11.27, U12.2, U12.27, U104.11, U201.13, U205.9, U212.13
RSLOT0: J1.d11, U42.7
RSLOT1: J1.d12, U42.9
RSLOT2: J1.d13, U43.7
RSLOT3: J1.d14, U43.9
RSLOT4: J1.d15, U44.7
RST1: U205.5, U205.12
RSTREQ: U201.9, U203.6
RUN1: U209.3, U209.19
RUN2: U209.18, U212.1
RUNPEND: U212.3, U212.4
SCLK: J1.c11, U200.2, U201.5, U202.9, U204.3, U206.3, U209.11, U213.3, U213.11
SF+: J1.c25, U28.7
SF-: J1.c26, U28.16
SL1: U202.11, U207.1
SL2: U202.3, U202.4
SPENT: U210.5, U211.8
SPRDRV: U102.3, U103.1
SPRNR: J1.c18, U94.14, U102.1
SPSEL: U210.4, U211.10
SQ0: U200.14, U201.1, U202.12
SQ0N: U201.2, U202.2
SQ1: U200.13, U201.11, U202.1
SQ1N: U201.10, U202.13
SQ2: U200.12, U203.1
SS0: U24.9, U42.4
SS1: U24.10, U42.12
SS2: U24.13, U43.4
SS3: U24.14, U43.12
SS4: U24.31, U44.4
STEP1: U209.5, U209.17
STEP2: U209.6, U209.16, U210.1
STEP3: U209.15, U211.1
STEPP: U211.3, U212.9
STRETCH: J1.c14, U201.3
STRN: U201.4, U203.2
SV0+: U101.9, U120.4
SV0-: U101.10, U120.12
SV1+: U101.13, U121.4
SV1-: U101.14, U121.12
SV2+: U101.31, U122.4
SV2-: U101.32, U122.12
SV3+: U101.35, U123.4
SV3-: U101.36, U123.12
TM0_0: U90.9, U93.3
TM0_1: U90.10, U93.4
TM0_2: U90.13, U93.5
TM0_3: U90.14, U93.6
TM0_4: U90.31, U93.7
TM1_0: U91.9, U93.16
TM1_1: U91.10, U93.17
TM1_2: U91.13, U93.18
TM1_3: U91.14, U93.19
TM1_4: U91.31, U93.20
TM2_0: U92.9, U93.26
TM2_1: U92.10, U93.27
TM2_2: U92.13, U93.28
TM2_3: U92.14, U93.29
TM2_4: U92.31, U93.30
TNZ0: U90.32, U93.38
TNZ1: U91.32, U93.39
TNZ2: U92.32, U93.40
TRAPDIV0: U28.29, U89.9, U95.39, U101.18
TRAPDIV0_N: U89.48, U95.31
U0: U19.19, U46.3
U1: U19.18, U46.4
U2: U19.17, U46.5
U3: U19.16, U46.6
U4: U19.15, U46.7
U5: U19.14, U46.16
UA0: J1.b30, U1.3, U2.3, U3.3, U4.3, U5.3, U6.3, U7.3, U105.18
UA1: J1.b31, U1.4, U2.4, U3.4, U4.4, U5.4, U6.4, U7.4, U105.16
UA2: J1.c1, U1.5, U2.5, U3.5, U4.5, U5.5, U6.5, U7.5, U105.14
UA3: J1.c2, U1.6, U2.6, U3.6, U4.6, U5.6, U6.6, U7.6, U105.12
UA4: J1.c3, U1.7, U2.7, U3.7, U4.7, U5.7, U6.7, U7.7, U105.9
UA5: J1.c4, U1.16, U2.16, U3.16, U4.16, U5.16, U6.16, U7.16, U105.7
UA6: J1.c5, U1.17, U2.17, U3.17, U4.17, U5.17, U6.17, U7.17, U105.5
UA7: J1.c6, U1.18, U2.18, U3.18, U4.18, U5.18, U6.18, U7.18, U105.3
UA8: J1.c7, U1.19, U2.19, U3.19, U4.19, U5.19, U6.19, U7.19, U106.18
UA9: J1.c9, U1.20, U2.20, U3.20, U4.20, U5.20, U6.20, U7.20, U106.16
UCZ: U19.13, U28.20
UN0: U19.2, U46.9
UN1: U19.3, U46.10
UN2: U19.4, U46.13
UN3: U19.5, U46.14
UN4: U19.6, U46.31
UN5: U19.7, U46.32
UNZ: U19.8, U46.35
UPC0: U14.19, U30.3, U31.3
UPC1: U14.18, U30.4, U31.4
UPC2: U14.17, U30.5, U31.5
UPC3: U14.16, U30.6, U31.6
UPC4: U14.15, U30.7, U31.7
UPC5: U14.14, U30.16, U31.16
UPC6: U14.13, U30.17, U31.17
UPC7: U14.12, U30.18, U31.18
UPC8: U15.19, U30.19, U31.19
UPC9: U15.18, U30.20, U31.20
WRAP: U53.39, U54.39, U55.39, U56.39, U57.39, U58.39, U59.4
WSTB: U206.5, U213.12
WSTB_NEXT: U206.2, U207.11
WSTB_PRE: U207.3, U207.12
